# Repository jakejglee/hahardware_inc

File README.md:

# hahardware_inc
Repo combining all work on hardware for the HA-HA Button project, from work during and after the SDP.

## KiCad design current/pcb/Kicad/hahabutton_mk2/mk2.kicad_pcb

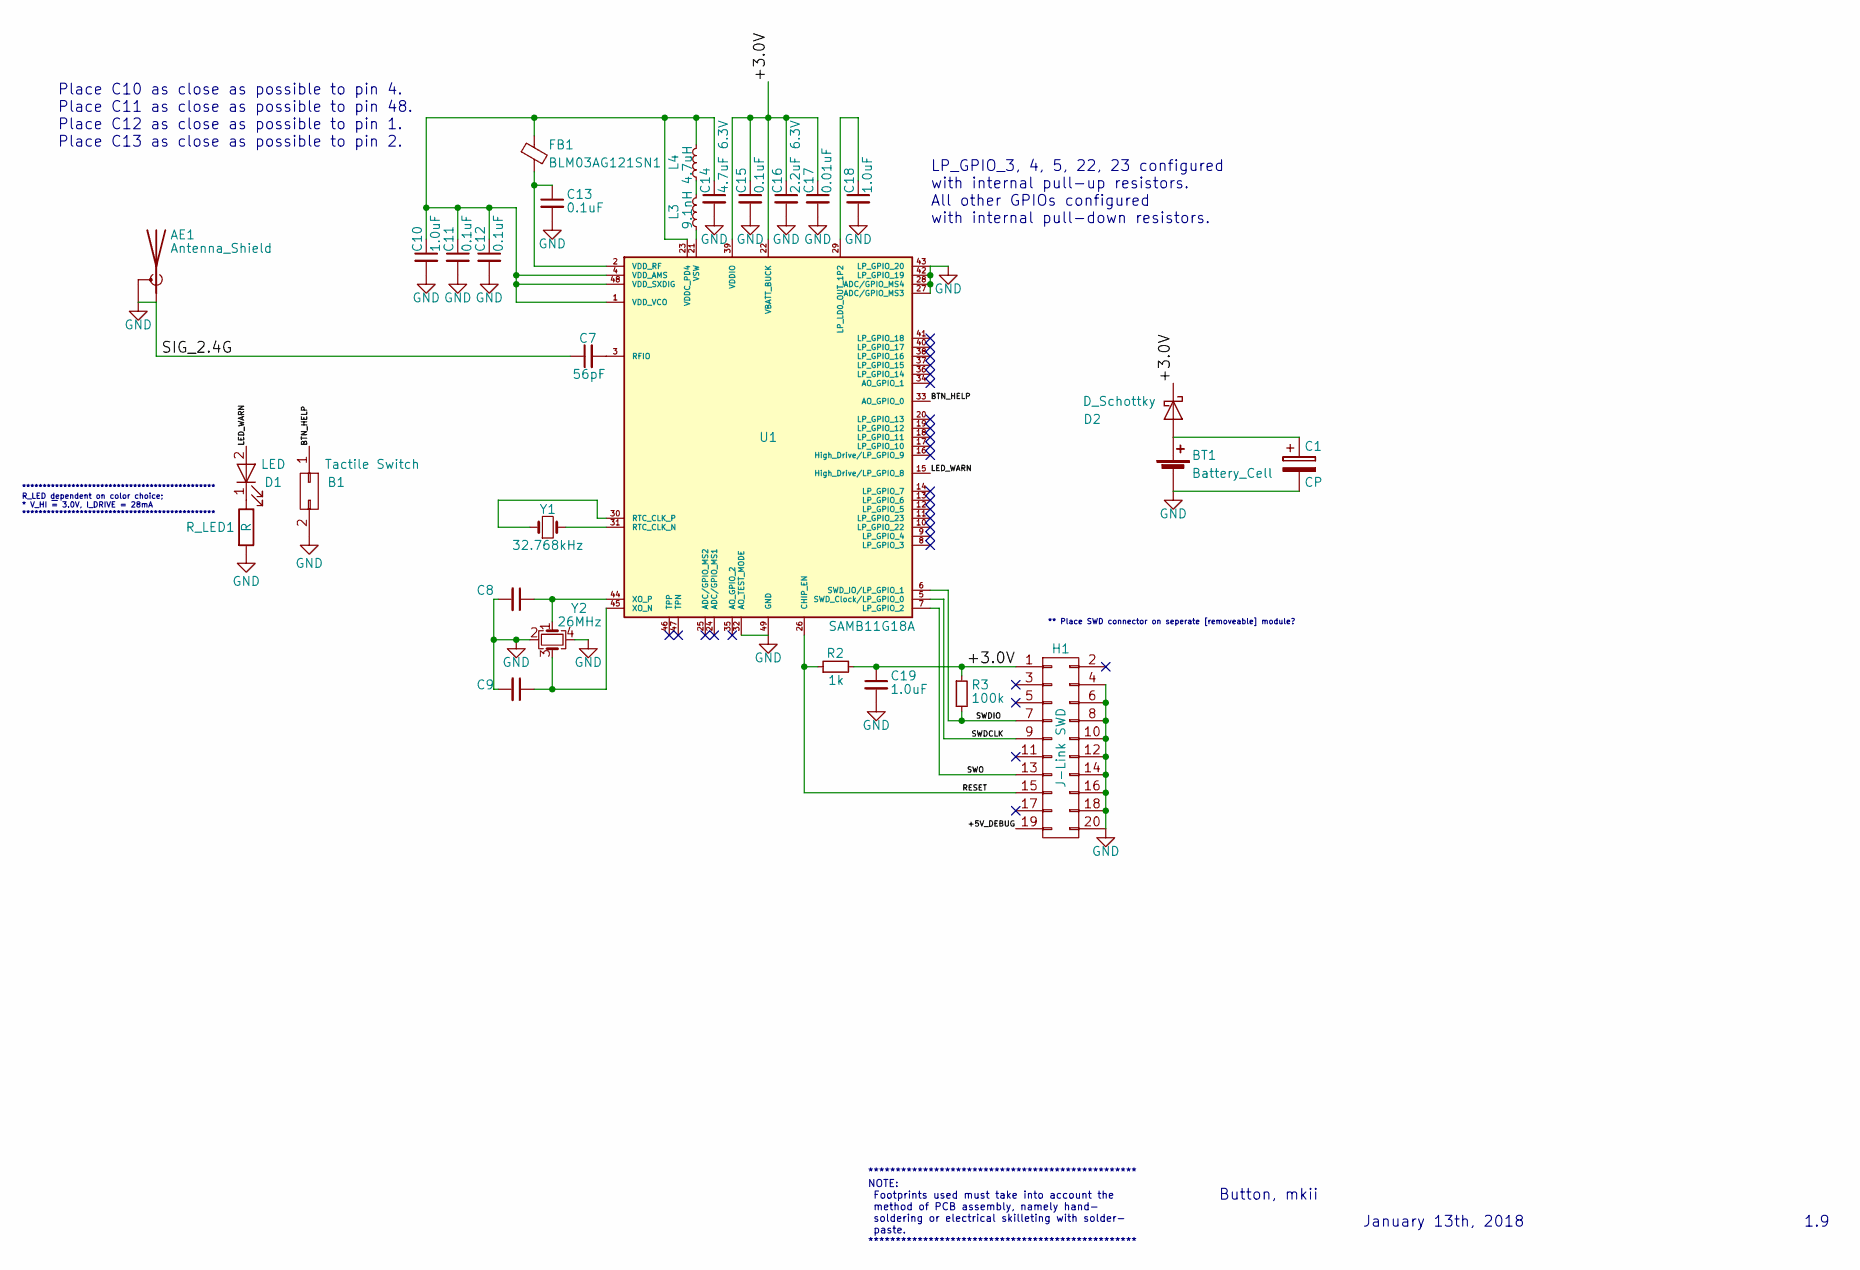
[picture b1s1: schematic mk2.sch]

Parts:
AE1: Antenna_Shield; 2p4GHzMIFA_cust
B1: Tactile Switch; SW_PUSH_6mm
BT1: Battery_Cell; batt_holder3035
C1: CP; C_0805
C7: 56pF; C_0402
C8, C9: C_Small; C_0402
C10, C18, C19: 1.0uF; C_0402
C11, C12, C13, C15: 0.1uF; C_0402
C14: 4.7uF 6.3V; C_0402
C16: 2.2uF 6.3V; C_0402
C17: 0.01uF; C_0402
D1: LED; LED_0402
D2: D_Schottky; D_0603
FB1: BLM03AG121SN1; C_0603_HandSoldering
H1: J-Link SWD; Socket_Strip_Straight_2x10_Pitch2.54mm_Drill0.889mm
L3: 9.1nH; C_0402
L4: 4.7uH; C_0805_HandSoldering
R2: 1k; C_0402
R3: 100k; C_0402
R_LED1: R; C_0402
U1: SAMB11G18A; QFN-48-1EP_6x6mm_Pitch0.4mm
Y1: 32.768kHz; Crystal_SMD_3215-2pin_3.2x1.5mm
Y2: 26MHz; Crystal_SMD_3225-4pin_3.2x2.5mm

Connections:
/+3.0V: C15.1, C16.1, C17.1, C19.1, D2.1 (K), H1.1, R2.2, R3.1, U1.22 (VBATT_BUCK), U1.39 (VDDIO)
/+5V_DEBUG: H1.19
/BTN_HELP: B1.1, U1.33 (AO_GPIO_0)
/LED_WARN: D1.2 (A), U1.15 (High_Drive/LP_GPIO_8)
/RESET: H1.15, R2.1, U1.26 (CHIP_EN)
/SWDCLK: H1.9, U1.5 (SWD_Clock/LP_GPIO_0)
/SWDIO: H1.7, R3.2, U1.6 (SWD_IO/LP_GPIO_1)
/SWO: H1.13, U1.7 (LP_GPIO_2)
GND: AE1.1 (A), AE1.2 (Shield), B1.2, BT1.2 (-), C1.2, C7.1, C8.2, C9.2, C10.2, C11.2, C12.2, C13.2, C14.2, C15.2, C16.2, C17.2, C18.2, C19.2, H1.4, H1.6, H1.8, H1.10, H1.12, H1.14, H1.16, H1.18, H1.20, R_LED1.2, U1.27 (ADC/GPIO_MS3), U1.28 (ADC/GPIO_MS4), U1.32 (AO_TEST_MODE), U1.42 (LP_GPIO_19), U1.43 (LP_GPIO_20), U1.49 (GND), Y2.2, Y2.4
unnamed: BT1.1 (+), C1.1, D2.2 (A)
unnamed: C7.2, U1.3 (RFIO)
unnamed: C8.1, U1.44 (XO_P), Y2.1
unnamed: C9.1, U1.45 (XO_N), Y2.3
unnamed: C10.1, C11.1, C12.1, C14.1, FB1.1, L4.2, U1.1 (VDD_VCO), U1.4 (VDD_AMS), U1.23 (VDDC_PD4), U1.48 (VDD_SXDIG)
unnamed: C13.1, FB1.2, U1.2 (VDD_RF)
unnamed: C18.1, U1.29 (LP_LD0_OUT_1P2)
unnamed: D1.1 (K), R_LED1.1
unnamed: L3.1, U1.21 (VSW)
unnamed: L3.2, L4.1
unnamed: U1.30 (RTC_CLK_P), Y1.1
unnamed: U1.31 (RTC_CLK_N), Y1.2

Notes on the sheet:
Button, mkii
Place C10 as close as possible to pin 4. Place C11 as close as possible to pin 48. Place C12 as close as possible to pin 1. Place C13 as close as possible to pin 2.
LP_GPIO_3, 4, 5, 22, 23 configured with internal pull-up resistors. All other GPIOs configured with internal pull-down resistors.
January 13th, 2018
1.9
*********************************************** R_LED dependent on color choice; * V_HI ~= 3.0V, I_DRIVE = 28mA ***********************************************
** Place SWD connector on seperate [removeable] module?
************************************************* NOTE: Footprints used must take into account the method of PCB assembly, namely hand- soldering or electrical skilleting with solder- paste. *************************************************

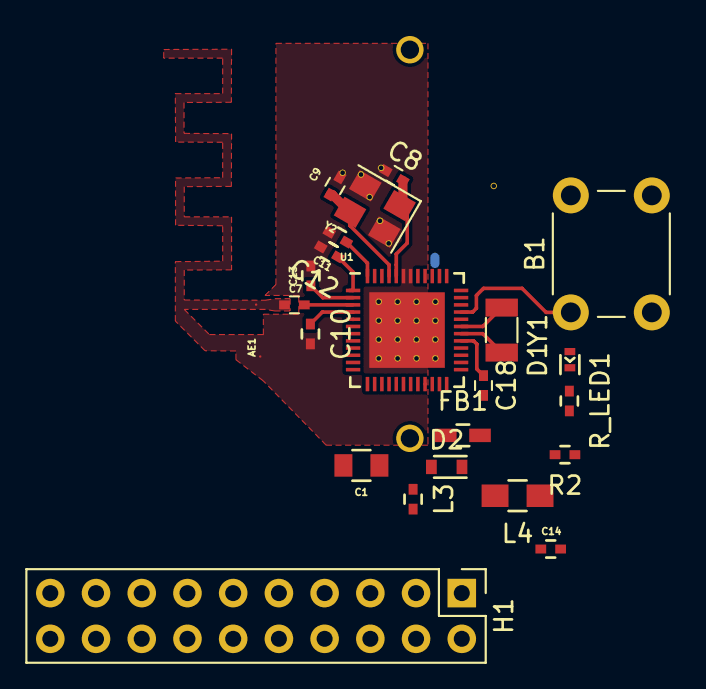
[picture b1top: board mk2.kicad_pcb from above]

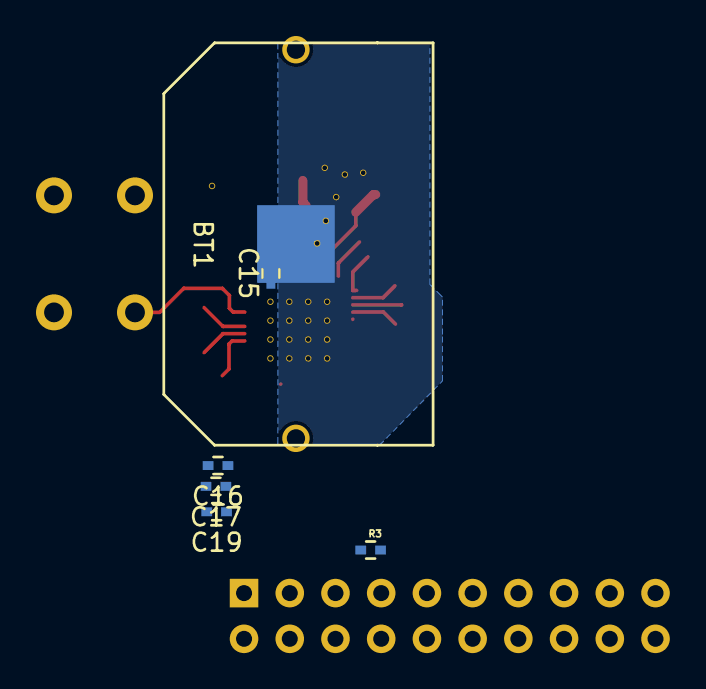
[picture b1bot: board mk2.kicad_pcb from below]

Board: 2 copper layers, 29 parts (6 on the bottom side), 20 nets.

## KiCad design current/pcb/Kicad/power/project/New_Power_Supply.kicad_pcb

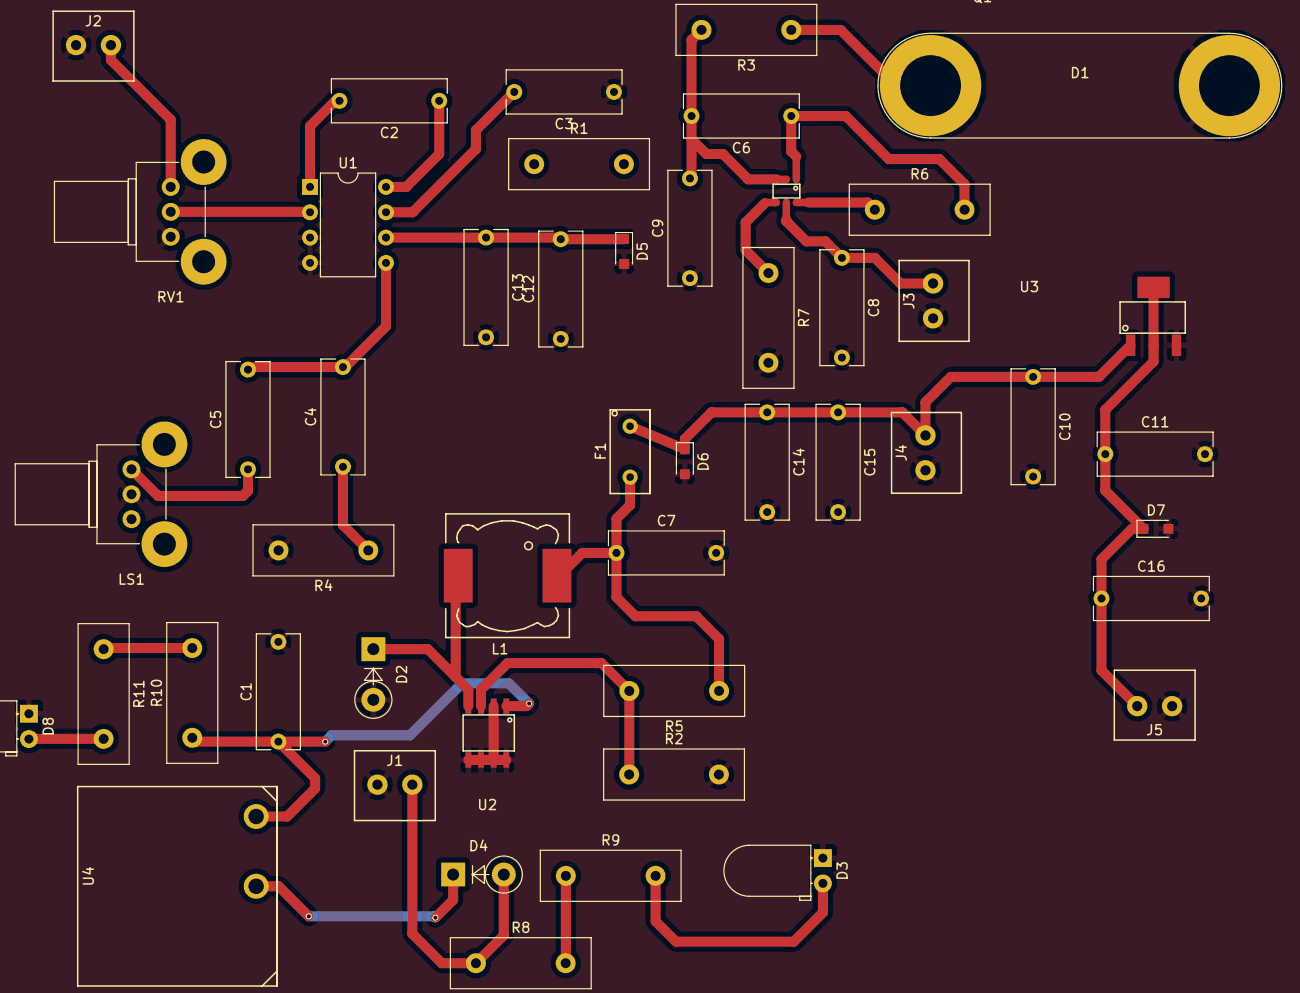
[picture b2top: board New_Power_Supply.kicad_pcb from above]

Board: 2 copper layers, 49 parts (0 on the bottom side), 27 nets.

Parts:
C1, C7, C9, C10, C11, C12, C14: 1u; C_Rect_L11.5mm_W4.3mm_P10.00mm_MKT
C2, C3, C8: 10u; C_Rect_L11.5mm_W4.3mm_P10.00mm_MKT
C4: 0.05u; C_Rect_L11.5mm_W4.3mm_P10.00mm_MKT
C5: 250u; C_Rect_L11.5mm_W4.3mm_P10.00mm_MKT
C6: 1000p; C_Rect_L11.5mm_W4.3mm_P10.00mm_MKT
C13, C15, C16: 0.1u; C_Rect_L11.5mm_W4.3mm_P10.00mm_MKT
D1: LED; Banana_Jack_2Pin
D2: D_Schottky; D_DO-15_P5.08mm_Vertical_KathodeUp
D3, D8: LED; LED_D5.0mm_Horizontal_O1.27mm_Z3.0mm
D4: D_Schottky_Small_ALT; D_DO-15_P5.08mm_Vertical_KathodeUp
D5: 12Vz; D_SOD-323_HandSoldering
D6, D7: 5 Vz; D_SOD-323_HandSoldering
F1: 0.5 AMPS; FuseTH500mA
J1, J2, J3, J4, J5: Screw_Terminal_1x02; OSTTEXX0164_2pin_3.5mm
L1: 39u; Choke_SMD_12x12mm_h4.5mm
LS1: Speaker; Potentiometer_Alps_RK09K_Vertical
Q1: Si3865DDV
R1, R9, R11: 1k; R_Box_L14.0mm_W5.0mm_P9.00mm
R2: 2k; R_Box_L14.0mm_W5.0mm_P9.00mm
R3: 14; R_Box_L14.0mm_W5.0mm_P9.00mm
R4: 10; R_Box_L14.0mm_W5.0mm_P9.00mm
R5: 3.3k; R_Box_L14.0mm_W5.0mm_P9.00mm
R6: 20k; R_Box_L14.0mm_W5.0mm_P9.00mm
R7: 10k; R_Box_L14.0mm_W5.0mm_P9.00mm
R8, R10: 220; R_Box_L14.0mm_W5.0mm_P9.00mm
RV1: 10k; Potentiometer_Alps_RK09K_Vertical
U1: LM386; DIP-8_W7.62mm
U2: AP1509
U3: LDO
U4: Switch

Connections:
+12V: C1.1, R1.1, R10.1, U2.1, U4.'1
GND: C1.2, C3.1, C7.2, C8.2, C9.1, C10.2, C11.2, C12.1, C13.2, C14.2, C15.2, C16.2, D1.1, D2.2, D3.1, D5.2, D6.2, D7.2, D8.1, J1.2, J2.2, J3.2, J4.2, J5.2, LS1.2, R2.2, R4.2, R7.2, RV1.3, U1.3, U1.4, U2.4, U2.5, U2.6, U2.7, U2.8, U3.1
unnamed: C2.1, U1.8
unnamed: C2.2, U1.1
unnamed: C3.2, U1.7
unnamed: C4.1, R4.1
unnamed: C4.2, C5.2, U1.5
unnamed: C5.1, LS1.1
unnamed: C6.1, Q1.6, R6.2
unnamed: C6.2, C9.2, Q1.2, Q1.3, R3.2
unnamed: C7.1, F1.2, L1.1, R5.1
unnamed: C8.1, J3.1, Q1.5
unnamed: C10.1, C14.1, C15.1, D6.1, F1.1, J4.1, U3.3
unnamed: C11.1, C16.1, D7.1, J5.1, U3.2, U3.4
unnamed: C12.2, C13.1, D5.1, Q1.4, R1.2, R6.1, U1.6
unnamed: D1.2, R3.1
unnamed: D2.1, L1.2, U2.3
unnamed: D3.2, R9.2
unnamed: D4.1, U4.1A
unnamed: D4.2, J1.1, R8.1
unnamed: D8.2, R11.2
unnamed: J2.1, RV1.1
unnamed: Q1.1, R7.1
unnamed: R2.1, R5.2, U2.2
unnamed: R8.2, R9.1
unnamed: R10.2, R11.1
unnamed: RV1.2, U1.2

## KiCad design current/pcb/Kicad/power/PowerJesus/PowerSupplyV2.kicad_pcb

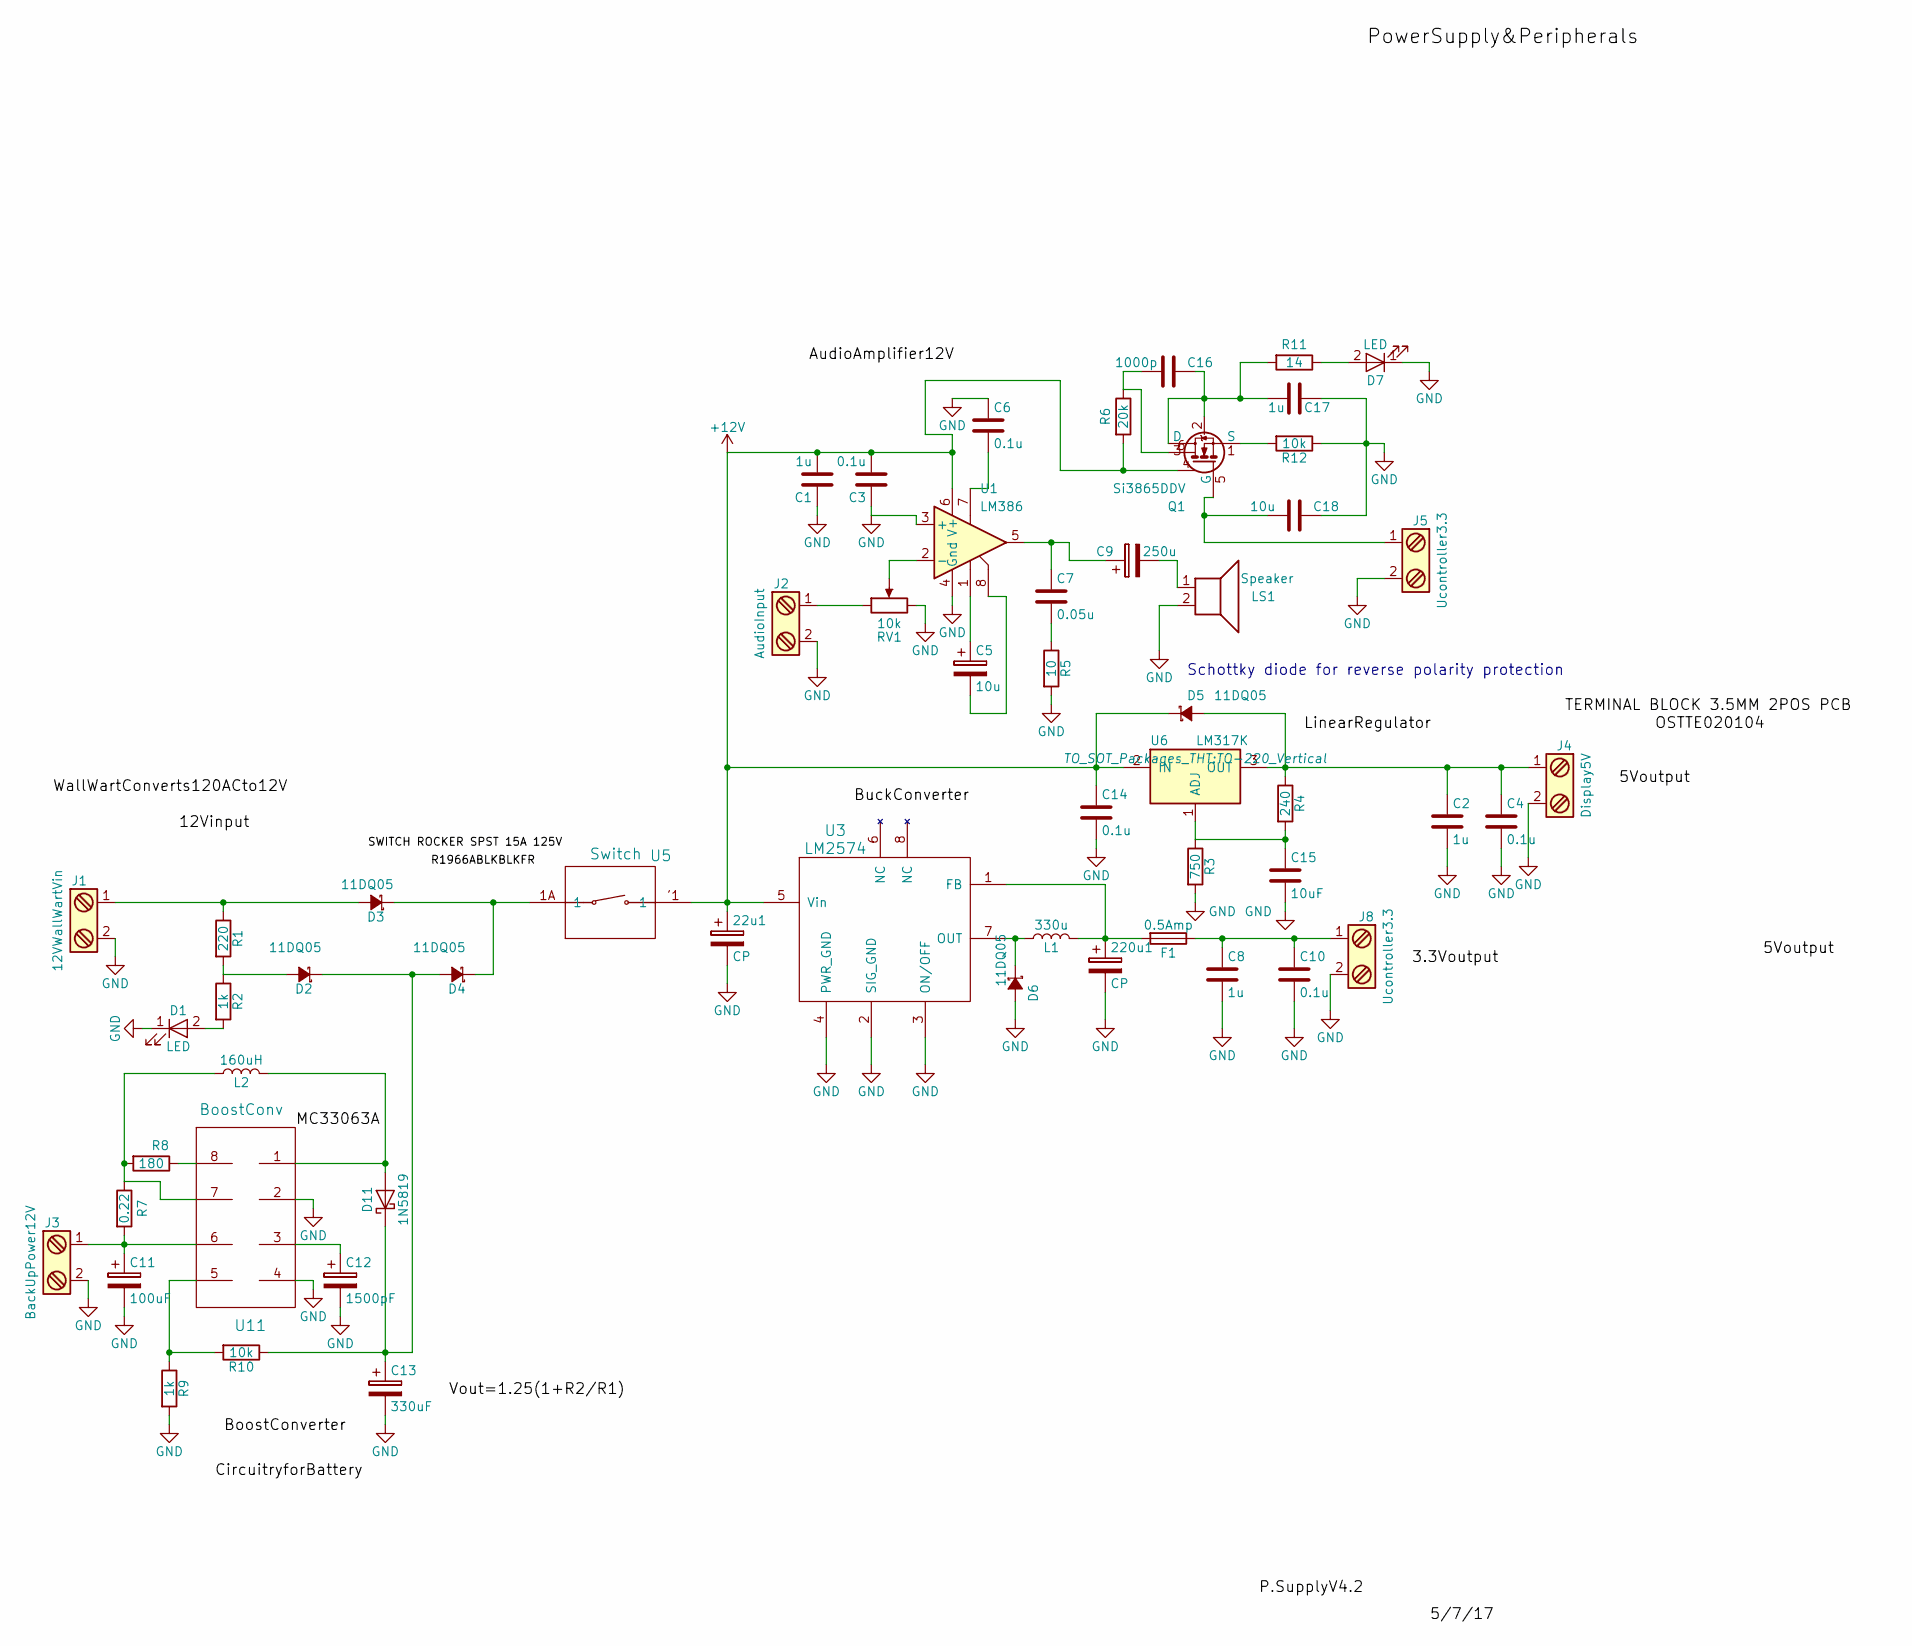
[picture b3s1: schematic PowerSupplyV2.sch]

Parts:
22u1, 220u1: CP; CP_Radial_D6.3mm_P2.50mm
C1, C2, C8, C17: 1u; R_Axial_DIN0204_L3.6mm_D1.6mm_P7.62mm_Horizontal
C3, C4, C6, C10, C14: 0.1u; R_Axial_DIN0204_L3.6mm_D1.6mm_P7.62mm_Horizontal
C5: 10u; CP_Radial_D6.3mm_P2.50mm
C7: 0.05u; C_0805_HandSoldering
C9: 250u; CP_Radial_D6.3mm_P2.50mm
C11: 100uF; CP_Radial_D6.3mm_P2.50mm
C12: 1500pF; CP_Radial_D6.3mm_P2.50mm
C13: 330uF; CP_Radial_D6.3mm_P2.50mm
C15: 10uF; R_Axial_DIN0204_L3.6mm_D1.6mm_P7.62mm_Horizontal
C16: 1000p; R_Axial_DIN0204_L3.6mm_D1.6mm_P7.62mm_Horizontal
C18: 10u; R_Axial_DIN0204_L3.6mm_D1.6mm_P7.62mm_Horizontal
D1, D7: LED; LED_D5.0mm_Horizontal_O1.27mm_Z3.0mm
D2, D3, D4, D5, D6: 11DQ05; D_DO-15_P5.08mm_Vertical_KathodeUp
D11: 1N5819; D_DO-15_P5.08mm_Vertical_KathodeUp
F1: 0.5Amp; FuseTH500mA
J1: 12VWallWartVin; BARREL_JACK
J2: AudioInput; BlockTerminal3.5mm
J3: BackUpPower12V; NIMH4.8V
J4: Display5V; BlockTerminal3.5mm
J5, J8: Ucontroller3.3; BlockTerminal3.5mm
L1: 330u; Choke_SMD_12x12mm_h4.5mm
L2: 160uH; Choke_SMD_12x12mm_h4.5mm
LS1: Speaker; BlockTerminal3.5mm
Q1: Si3865DDV
R1: 220; R_Axial_DIN0309_L9.0mm_D3.2mm_P2.54mm_Vertical
R2, R9: 1k; R_Axial_DIN0309_L9.0mm_D3.2mm_P2.54mm_Vertical
R3: 750; R_Axial_DIN0309_L9.0mm_D3.2mm_P2.54mm_Vertical
R4: 240; R_Axial_DIN0309_L9.0mm_D3.2mm_P2.54mm_Vertical
R5: 10; R_0805_HandSoldering
R6: 20k; R_Axial_DIN0309_L9.0mm_D3.2mm_P2.54mm_Vertical
R7: 0.22; R_Axial_DIN0309_L9.0mm_D3.2mm_P2.54mm_Vertical
R8: 180; R_Axial_DIN0309_L9.0mm_D3.2mm_P2.54mm_Vertical
R10, R12: 10k; R_Axial_DIN0309_L9.0mm_D3.2mm_P2.54mm_Vertical
R11: 14; R_Axial_DIN0309_L9.0mm_D3.2mm_P2.54mm_Vertical
RV1: 10k; Potentiometer_Alps_RK09K_Vertical
U1: LM386; DIP-8_W7.62mm
U3: LM2574; PDIP-8
U5: Switch
U6: LM317K; TO-220_Vertical
U11: BoostConv; DIP-8_W7.62mm

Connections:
+12V: 22u1.1, C1.2, C3.2, C14.1, D5.1 (K), Q1.4, R6.2, U1.6 (V+), U3.5 (Vin), U5.'1, U6.2 (IN)
GND: 22u1.2, 220u1.2, C1.1, C2.2, C3.1, C4.2, C6.1, C8.2, C10.2, C11.2, C12.2, C13.2, C14.2, C15.2, C17.1, C18.1, D1.1 (K), D6.2 (A), D7.1 (K), J1.2, J2.2, J3.2, J4.2, J5.2, J8.2, LS1.2, R3.2, R5.2, R9.2, R12.1, RV1.3, U1.3 (+), U1.4 (Gnd), U3.2 (SIG_GND), U3.3 (ON/OFF), U3.4 (PWR_GND), U11.2, U11.4
unnamed: 220u1.1, F1.2, L1.2, U3.1 (FB)
unnamed: C2.1, C4.1, D5.2 (A), J4.1, R4.1, U6.3 (OUT)
unnamed: C5.1, U1.1
unnamed: C5.2, U1.8
unnamed: C6.2, U1.7
unnamed: C7.1, C9.1, U1.5
unnamed: C7.2, R5.1
unnamed: C9.2, LS1.1
unnamed: C8.1, C10.1, F1.1, J8.1
unnamed: C11.1, J3.1, R7.2, U11.6
unnamed: C12.1, U11.3
unnamed: C13.1, D2.1 (K), D4.2 (A), D11.1 (K), R10.1
unnamed: C15.1, R3.1, R4.2, U6.1 (ADJ)
unnamed: C16.1, C17.2, Q1.2, Q1.3 (D), R11.2
unnamed: C16.2, Q1.6, R6.1
unnamed: C18.2, J5.1, Q1.5 (G)
unnamed: D1.2 (A), R2.2
unnamed: D2.2 (A), R1.2, R2.1
unnamed: D3.1 (K), D4.1 (K), U5.1A
unnamed: D3.2 (A), J1.1, R1.1
unnamed: D6.1 (K), L1.1, U3.7 (OUT)
unnamed: D7.2 (A), R11.1
unnamed: D11.2 (A), L2.2, U11.1
unnamed: J2.1, RV1.1
unnamed: L2.1, R7.1, R8.2, U11.7
unnamed: Q1.1 (S), R12.2
unnamed: R8.1, U11.8
unnamed: R9.1, R10.2, U11.5
unnamed: RV1.2, U1.2 (-)

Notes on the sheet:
Schottky diode for reverse polarity protection

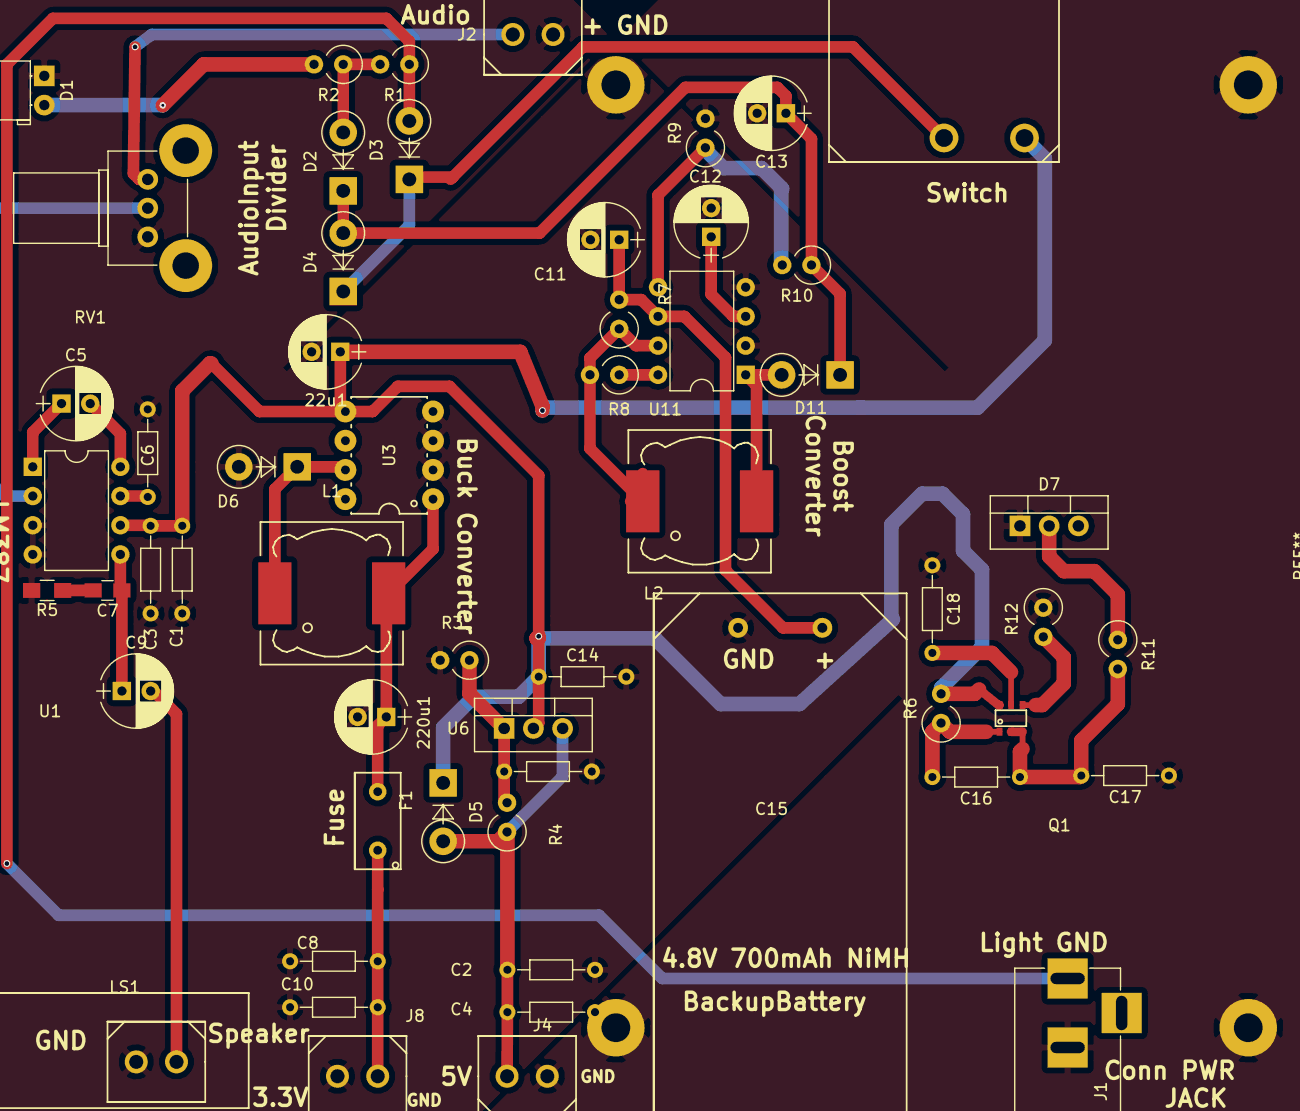
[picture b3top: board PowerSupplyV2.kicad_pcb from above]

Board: 2 copper layers, 56 parts (0 on the bottom side), 31 nets.

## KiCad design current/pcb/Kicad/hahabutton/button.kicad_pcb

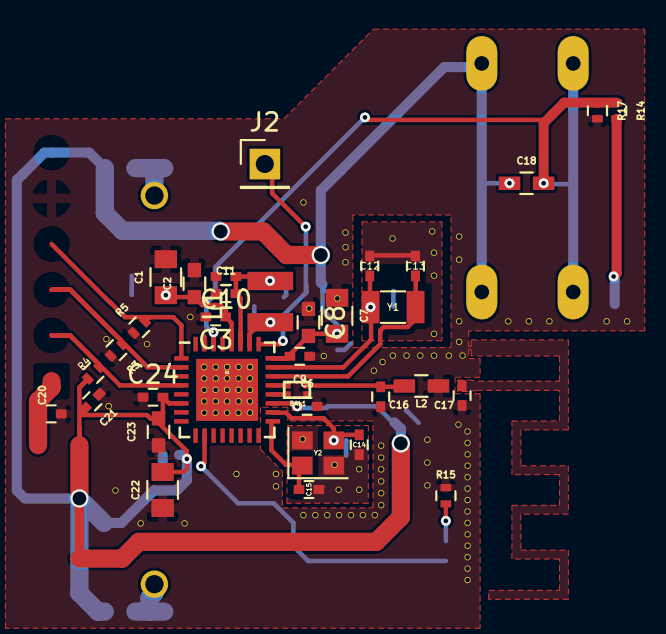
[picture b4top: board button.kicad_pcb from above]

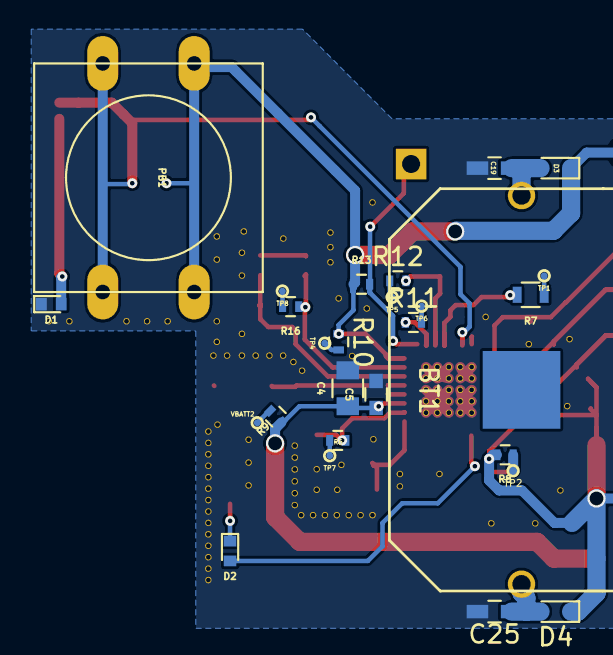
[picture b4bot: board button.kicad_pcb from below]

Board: 2 copper layers, 61 parts (27 on the bottom side), 30 nets.

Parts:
BAL1: STBNR1_balun; BNRG1_balun
BT1: Battery_cc3035; batt_holder3035
C1, C22: 1uF; C_0805
C2, C23: 0.1uF; C_0603
C3, C24: 0.01uF; C_0402
C4, C7: 0.01uF; C_0805
C5, C8: 1000pF; C_0603
C6, C9: 10pF; C_0402
C10: 0.1uF; C_0402
C11: 100pF; C_0402
C12, C14: 27pF; C_0402
C13: 22pF; C_0402
C15: 33pF; C_0402
C16, C17: TBD; C_0402
C18, C19, C25: 1uF; C_0603_HandSoldering
C20, C21: 1uF; C_0402
D1: LED (Green-1); LED_0402
D2: LED (Green-2); LED_0402
D3, D4: Power thru Battery; D_0603
J2: RESET_CONN; Pin_Header_Straight_1x01_Pitch2.54mm
L1: 10uH; Neosid_Inductor_SM-NE29_SMD1008
L2: L; C_0603_HandSoldering
PB1: pb_v2; SW_PUSH-12mm
R3, R4, R5, R13, R17: 100k; R_0402
R6, R8, R9, R10, R11, R12, R14, R15, R16: 1k; R_0402
R7: 1k; R_0603
TP1: VDD1V2; Measurement_Point_Round-SMD-tiniest
TP2, TP4: VBATT3; Measurement_Point_Round-SMD-tiniest
TP5: SMSPFILT2; Measurement_Point_Round-SMD-tiniest
TP6: SMPSFILT1; Measurement_Point_Round-SMD-tiniest
TP7: Xtal32MHz; Measurement_Point_Round-SMD-tiniest
TP8: Xtal32kHz; Measurement_Point_Round-SMD-tiniest
U1: STBlueNRG-1; STBNRG1
VBATT2: VBATT2; Measurement_Point_Round-SMD-tiniest
Y1: Xtal 32.768kHz; Crystal_SMD_3215-2pin_3.2x1.5mm
Y2: XTAL 32MHz; Crystal_SMD_2520-4pin_2.5x2.0mm

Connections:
+3V3: C4.1, C5.1, C6.1, C7.2, C8.2, C9.2, C18.1, C21.2, C22.2, C23.2, C24.2, D3.1, D4.1, PB1.1, R4.1, R8.2, R9.1, R10.1, R13.1, U1.6, U1.19, U1.24
/DIO2_LED: D2.2, U1.10
/DIO12_BUTTON: C18.2, PB1.2, R14.1, R17.1, U1.30
/RF0: BAL1.1, U1.21
/RF1: BAL1.2, U1.20
DIO7: R4.2, U1.4
DIO9: R3.1, U1.2
DIO10: R5.2, U1.1
GND: BAL1.4, C1.2, C2.2, C3.2, C4.2, C5.2, C6.2, C7.1, C8.1, C9.1, C10.2, C11.1, C12.1, C13.1, C14.1, C15.1, C16.2, C17.1, C17.2, C19.2, C20.1, C21.1, C22.1, C23.1, C24.1, C25.2, D1.1, L2.2, R3.2, R5.1, R15.2, R17.2, U1.31, U1.33, Y2.2, Y2.4
unnamed: BAL1.3, C16.1, L2.1
unnamed: BT1.1, C19.1, D3.2
unnamed: BT1.2, C25.1, D4.2
unnamed: C1.1, C2.1, C3.1, R7.2, U1.28
unnamed: C10.1, C11.2, L1.2, R12.2, U1.27
unnamed: C12.2, R16.1, U1.23, Y1.1
unnamed: C13.2, U1.22, Y1.2
unnamed: C14.2, R6.1, U1.18, Y2.3
unnamed: C15.2, U1.17, Y2.1
unnamed: D1.2, R14.2
unnamed: D2.1, R15.1
unnamed: J2.1, R13.2, U1.25
unnamed: L1.1, R11.1, U1.26
unnamed: R6.2, TP7.1
unnamed: R7.1, TP1.1
unnamed: R8.1, TP2.1
unnamed: R9.2, VBATT2.1
unnamed: R10.2, TP4.1
unnamed: R11.2, TP6.1
unnamed: R12.1, TP5.1
unnamed: R16.2, TP8.1

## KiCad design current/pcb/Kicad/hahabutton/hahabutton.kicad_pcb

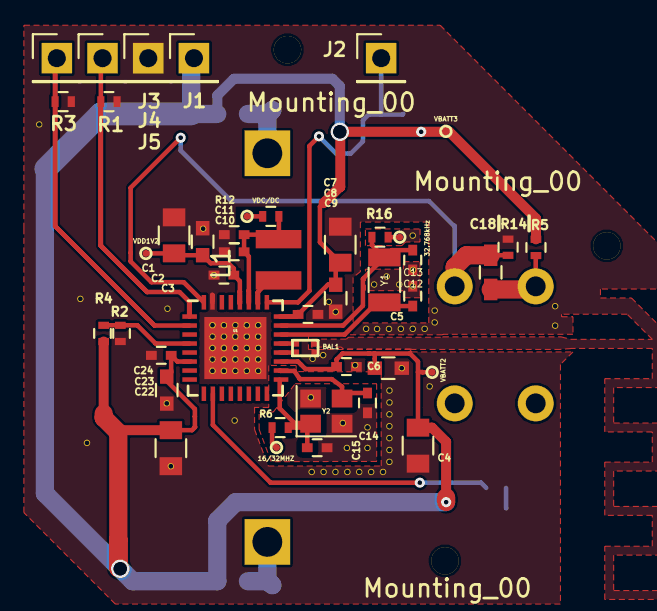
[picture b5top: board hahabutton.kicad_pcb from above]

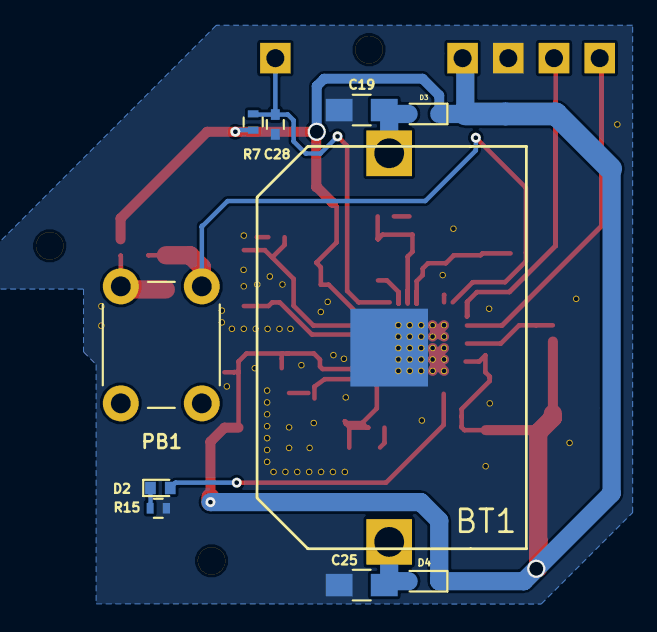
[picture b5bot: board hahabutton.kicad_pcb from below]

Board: 2 copper layers, 57 parts (10 on the bottom side), 24 nets.

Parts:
16/32MHZ: Xtal32MHz; Measurement_Point_Round-SMD-tiniest
32.768kHz: Xtal32kHz; Measurement_Point_Round-SMD-tiniest
BAL1: STBNR1_balun; BNRG1_balun
BT1: Battery_cc3035; batt_holder3035
C1, C4, C22: 1uF; C_0805
C2, C5, C23: 0.1uF; C_0603
C3, C6, C24: 0.01uF; C_0402
C7: 0.01uF; C_0805
C8: 1000pF; C_0603
C9: 10pF; C_0402
C10: 0.1uF; C_0402
C11: 100pF; C_0402
C12, C14: 27pF; C_0402
C13: 22pF; C_0402
C15: 33pF; C_0402
C18: 1uF; C_0603_HandSoldering
C19, C25: 1uF; C_0805_HandSoldering
C28: 10nF; C_0402
D2: LED (Green-2); LED_0402
D3, D4: Power thru Battery; D_0603
J1: VREF_CONN; Pin_Header_Straight_1x01_Pitch2.54mm
J2: RESET_CONN; Pin_Header_Straight_1x01_Pitch2.54mm
J3: GND_CONN; Pin_Header_Straight_1x01_Pitch2.54mm
J4: SWDIO_CONN; Pin_Header_Straight_1x01_Pitch2.54mm
J5: SWDCLK_CONN; Pin_Header_Straight_1x01_Pitch2.54mm
L1: 10uH; Neosid_Inductor_SM-NE29_SMD1008
Mounting_00, Mounting_00#2, Mounting_00#3: 1pin
PB1: pb_v2; SW_PUSH_6mm
R1, R2, R3, R4, R5, R7: 100k; R_0402
R6, R12, R16: 1k; R_0402
R14: 100; R_0402
R15: 50; R_0402
U1: STBlueNRG-1; STBNRG1
VBATT2: VBATT2; Measurement_Point_Round-SMD-tiniest
VBATT3: VBATT3; Measurement_Point_Round-SMD-tiniest
VDC/DC: SMSPFILT2; Measurement_Point_Round-SMD-tiniest
VDD1V2: VDD1V2; Measurement_Point_Round-SMD-tiniest
Y1: Xtal 32.768kHz; Crystal_SMD_3215-2pin_3.2x1.5mm
Y2: XTAL 32MHz; Crystal_SMD_2520-4pin_2.5x2.0mm

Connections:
+3V3: C4.1, C5.1, C6.1, C7.2, C8.2, C9.2, C22.2, C23.2, C24.2, D3.1, D4.1, J1.1, R4.1, R5.1, R7.1, U1.6, U1.19, U1.24, VBATT2.1, VBATT3.1
/DIO2_LED: D2.2, U1.10
/DIO12_BUTTON: C18.2, PB1.2, R14.1, U1.32
/RF0: BAL1.1, U1.21
/RF1: BAL1.2, U1.20
DIO7: R2.1, R4.2, U1.4
DIO9: J5.1, R3.1, U1.2
DIO10: J4.1, R1.1, U1.1
GND: BAL1.3, BAL1.4, BT1.3, C1.2, C2.2, C3.2, C4.2, C5.2, C6.2, C7.1, C8.1, C9.1, C10.2, C11.1, C12.1, C13.1, C14.1, C15.1, C19.2, C22.1, C23.1, C24.1, C25.2, C28.1, J3.1, R1.2, R2.2, R3.2, R14.2, R15.2, U1.31, U1.33, Y2.2, Y2.4
unnamed: BT1.1, C19.1, D3.2
unnamed: BT1.2, C25.1, D4.2
unnamed: C1.1, C2.1, C3.1, U1.28, VDD1V2.1
unnamed: C10.1, C11.2, L1.2, R12.2, U1.27
unnamed: C12.2, R16.1, U1.23, Y1.1
unnamed: C13.2, U1.22, Y1.2
unnamed: C14.2, U1.18, Y2.3
unnamed: C15.2, R6.1, U1.17, Y2.1
unnamed: C18.1, PB1.1, R5.2
unnamed: C28.2, J2.1, R7.2, U1.25
unnamed: D2.1, R15.1
unnamed: L1.1, U1.26
unnamed: 16/32MHZ.1, R6.2
unnamed: R12.1, VDC/DC.1
unnamed: 32.768kHz.1, R16.2

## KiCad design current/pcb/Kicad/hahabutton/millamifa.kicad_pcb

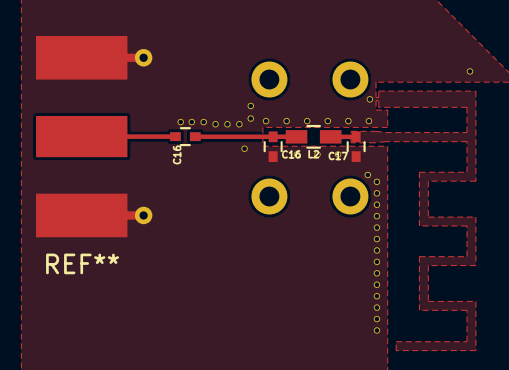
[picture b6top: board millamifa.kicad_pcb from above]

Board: 2 copper layers, 5 parts (1 on the bottom side), 2 nets.

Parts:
C16, C16#2, C17: TBD; C_0402
L2: TBD; C_0603_HandSoldering
PB1: pb_v2; SW_PUSH_6mm

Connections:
GND: C16#2.2, C17.1, C17.2, L2.2
unnamed: C16.1, C16#2.1, L2.1

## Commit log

2017-12-09 restructured from "hahardware"
2017-12-26 continued work on hahabutton_mkii; reorganized...
2018-01-02 work on MIFA footprint begins...
2018-01-02 more work on MIFA footprint...
2018-01-03 antenna stencil made; began layout.
2018-01-04 taking form, mkii...
2018-01-14 not much change...
2018-01-16 fixed footprint paths; the progression to 2.0 continues...
